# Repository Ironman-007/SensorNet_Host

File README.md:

# SensorNet_Host

### Platform: VSCode + Platformio

- Host node for the SensorNet project
- Host or nodes need to be burned with Arduino bootloader first.

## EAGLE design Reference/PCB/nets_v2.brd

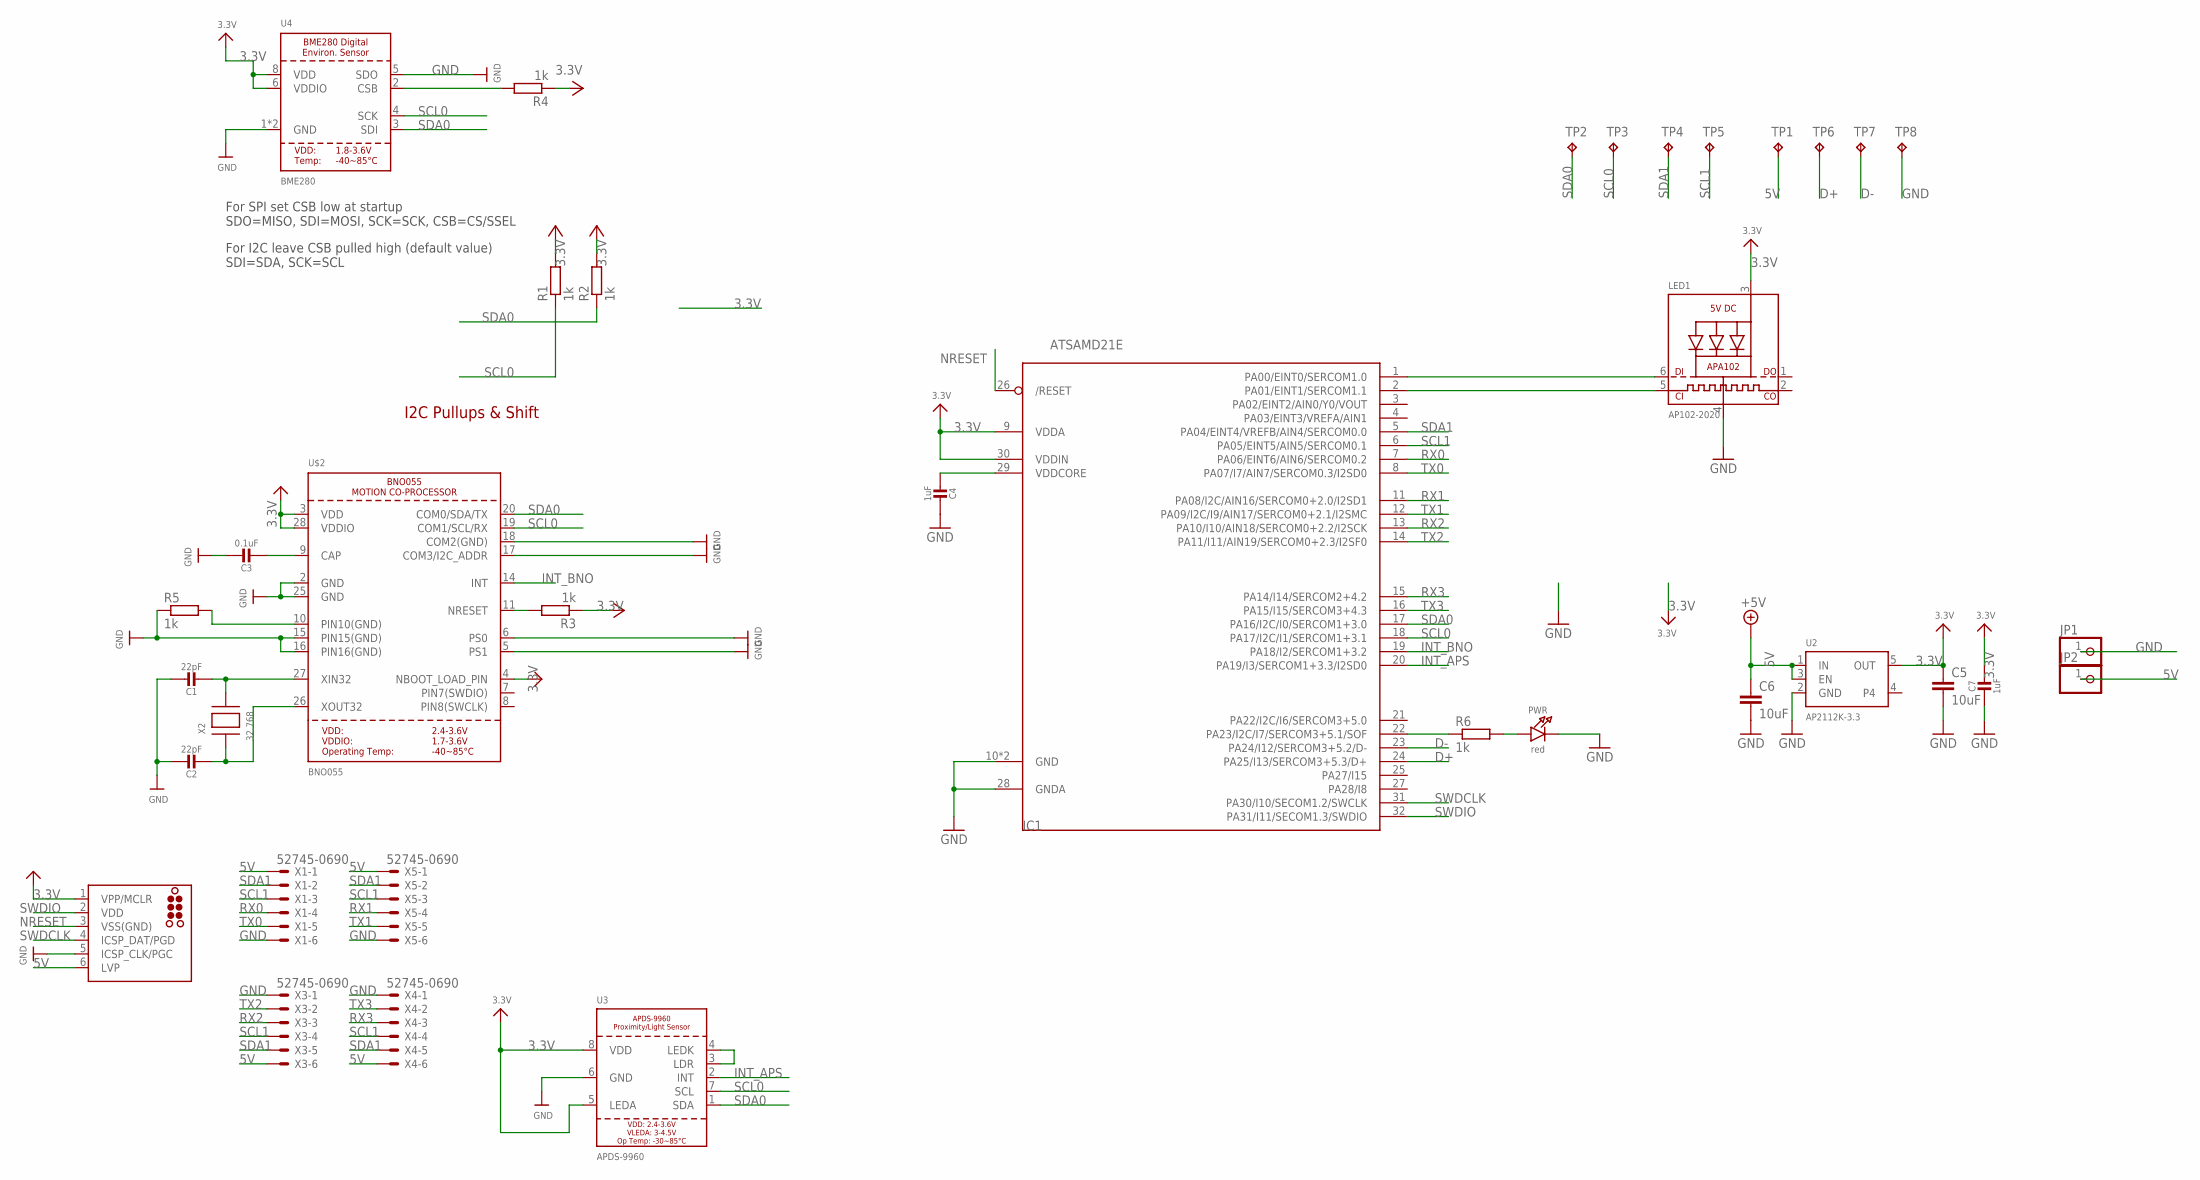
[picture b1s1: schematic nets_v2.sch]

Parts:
C1, C2: 22pF; _0402NO; MPN 885012005042
C3: 0.1uF; _0402NO; MPN R79IC3100Z340J
C4, C7: 1uF; _0402NO
C5, C6: 10uF; C0603
IC1: ATSAMD21E; QFN32_5MM
J1: TC2030-ICSP-MCP-NL; TC2030-MCP-NL
JP1, JP2: PINHD-1X1; 1X01
LED1: AP102-2020; APA102_2020
PWR: red; CHIPLED_0603_NOOUTLINE
R1, R2, R3, R4, R5, R6: 1k; R0402
TP1, TP2, TP3, TP4, TP5, TP6, TP7, TP8: TPTP10R; TP10R
U2: AP2112K-3.3; SOT23-5
U3: APDS-9960
U4: BME280
U$2: BNO055
X1, X3, X4, X5: 52745-0690
X2: 32.768; XTAL3215

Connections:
3.3V: C5.1, C7.1, IC1.9 (VDDA), IC1.30 (VDDIN), J1.1 (VPP/MCLR), LED1.3 (VDD), R1.2, R2.2, R3.1, R4.1, U2.5 (OUT), U3.5 (LEDA), U3.8 (VDD), U4.6 (VDDIO), U4.8 (VDD), U$2.3 (VDD), U$2.4 (NBOOT_LOAD_PIN), U$2.28 (VDDIO)
5V: C6.1, J1.6 (LVP), JP2.1, TP1.TP, U2.1 (IN), U2.3 (EN), X1.1, X3.6, X4.6, X5.1
D+: IC1.24 (PA25/I13/SERCOM3+5.3/D+), TP6.TP
D-: IC1.23 (PA24/I12/SERCOM3+5.2/D-), TP7.TP
GND: C1.1, C2.1, C3.1, C4.1, C5.2, C6.2, C7.2, IC1.10 (GND), IC1.28 (GNDA), IC1.33 (GND), J1.5 (ICSP_CLK/PGC), JP1.1, LED1.4 (GND), PWR.C, R5.1, TP8.TP, U2.2 (GND), U3.6 (GND), U4.1 (GND), U4.5 (SDO), U4.7 (GND), U$2.2 (GND), U$2.5 (PS1), U$2.6 (PS0), U$2.15 (PIN15(GND)), U$2.16 (PIN16(GND)), U$2.17 (COM3/I2C_ADDR), U$2.18 (COM2(GND)), U$2.25 (GND), X1.6, X3.1, X4.1, X5.6
INT_APS: IC1.20 (PA19/I3/SERCOM1+3.3/I2SD0), U3.2 (INT)
INT_BNO: IC1.19 (PA18/I2/SERCOM1+3.2), U$2.14 (INT)
unnamed: C1.2, U$2.27 (XIN32), X2.P$2
unnamed: C2.2, U$2.26 (XOUT32), X2.P$1
unnamed: C3.2, U$2.9 (CAP)
unnamed: PWR.A, R6.2
unnamed: U3.3 (LDR), U3.4 (LEDK)
unnamed: R5.2, U$2.10 (PIN10(GND))
unnamed: R3.2, U$2.11 (NRESET)
unnamed: R4.2, U4.2 (CSB)
unnamed: IC1.1 (PA00/EINT0/SERCOM1.0), LED1.6 (DI)
unnamed: IC1.22 (PA23/I2C/I7/SERCOM3+5.1/SOF), R6.1
unnamed: IC1.2 (PA01/EINT1/SERCOM1.1), LED1.5 (CKI)
NRESET: IC1.26 (/RESET), J1.3 (VSS(GND))
RX0: IC1.7 (PA06/EINT6/AIN6/SERCOM0.2), X1.4
RX1: IC1.11 (PA08/I2C/AIN16/SERCOM0+2.0/I2SD1), X5.4
RX2: IC1.13 (PA10/I10/AIN18/SERCOM0+2.2/I2SCK), X3.3
RX3: IC1.15 (PA14/I14/SERCOM2+4.2), X4.3
SCL0: IC1.18 (PA17/I2C/I1/SERCOM1+3.1), R1.1, TP3.TP, U3.7 (SCL), U4.4 (SCK), U$2.19 (COM1/SCL/RX)
SCL1: IC1.6 (PA05/EINT5/AIN5/SERCOM0.1), TP5.TP, X1.3, X3.4, X4.4, X5.3
SDA0: IC1.17 (PA16/I2C/I0/SERCOM1+3.0), R2.1, TP2.TP, U3.1 (SDA), U4.3 (SDI), U$2.20 (COM0/SDA/TX)
SDA1: IC1.5 (PA04/EINT4/VREFB/AIN4/SERCOM0.0), TP4.TP, X1.2, X3.5, X4.5, X5.2
SWDCLK: IC1.31 (PA30/I10/SECOM1.2/SWCLK), J1.4 (ICSP_DAT/PGD)
SWDIO: IC1.32 (PA31/I11/SECOM1.3/SWDIO), J1.2 (VDD)
TX0: IC1.8 (PA07/I7/AIN7/SERCOM0.3/I2SD0), X1.5
TX1: IC1.12 (PA09/I2C/I9/AIN17/SERCOM0+2.1/I2SMC), X5.5
TX2: IC1.14 (PA11/I11/AIN19/SERCOM0+2.3/I2SF0), X3.2
TX3: IC1.16 (PA15/I15/SERCOM3+4.3), X4.2
VDDCORE: C4.2, IC1.29 (VDDCORE)

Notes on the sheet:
I2C Pullups & Shift
For SPI set CSB low at startup SDO=MISO, SDI=MOSI, SCK=SCK, CSB=CS/SSEL
For I2C leave CSB pulled high (default value) SDI=SDA, SCK=SCL

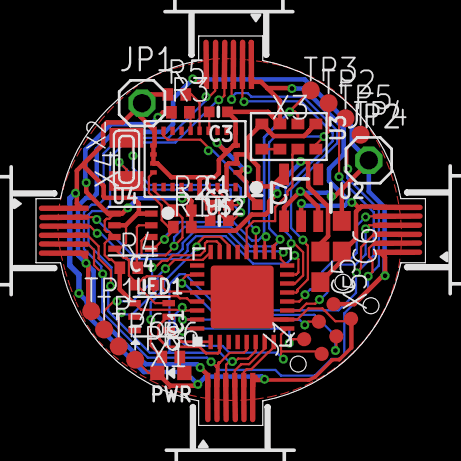
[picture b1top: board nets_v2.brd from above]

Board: 2 copper layers, 21.6 x 21.6 mm, 36 parts (0 on the bottom side), 34 nets.

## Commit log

2024-05-24 udated by FZ
2024-06-01 udated by FZ: BLE send data working
2024-06-03 udated by FZ: added reading sensor network, to be tested.
2024-06-03 udated by FZ: why the I2C scan is not working?.
2024-06-03 udated by FZ: solve I2C problem, to be tested the reading data from nodes.
2024-06-04 udated by FZ: reading nodes and send dat working, data to be parsed.
2024-06-04 udated by FZ: add node number to the data frame (first two bytes).

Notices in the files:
parts and their libraries:
microbuilder: This work is placed in the public domain, and may be freely used for commercial and non-commercial work with the following conditions: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
tag-connect-2030: ©2009 ROFA.cz - modified and updated by Robert Darlington ‹rdarlington@gmail.com›
